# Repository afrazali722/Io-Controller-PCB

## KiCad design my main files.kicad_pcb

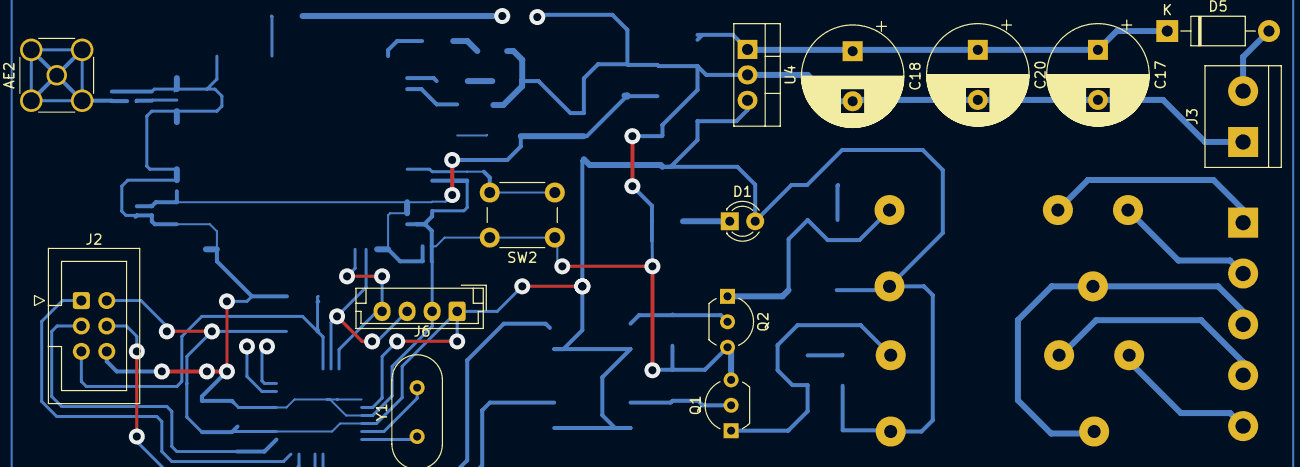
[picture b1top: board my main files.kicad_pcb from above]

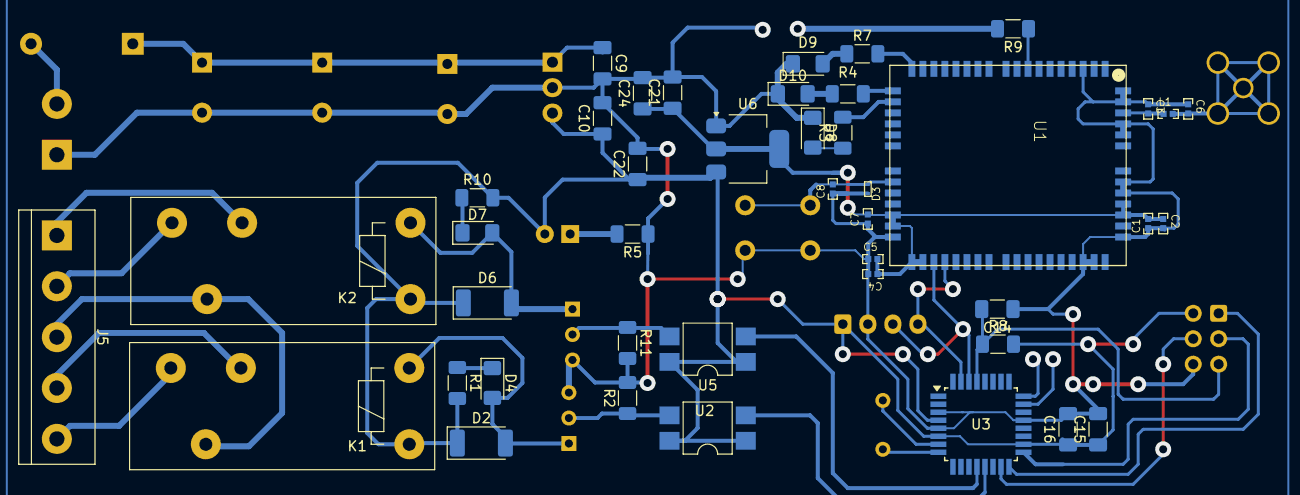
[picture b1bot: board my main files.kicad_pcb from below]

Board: 2 copper layers, 57 parts (43 on the bottom side), 37 nets.

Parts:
AE2: Antenna_Shield; SMA_Wurth_60312002114503_Vertical
C1, C4: 2.2uF; C0402
C2, C5, C7: 0.1uF; C0402
C3, C6: NC; C0402
C8: 330pF; C0402
C9, C14, C16, C22: 1uF; C_1206_3216Metric_Pad1.33x1.80mm_HandSolder
C10, C21: 10uF; C_1206_3216Metric_Pad1.33x1.80mm_HandSolder
C15, C24: 100nF; C_1206_3216Metric_Pad1.33x1.80mm_HandSolder
C17, C18, C20: 4700uF; CP_Radial_D10.0mm_P5.00mm
D1: LED; LED_D3.0mm
D2, D6: SM4007; D_MELF
D3: ESD7951ST5G; SOD−923
D4, D7, D8, D9, D10: LED; LED_1206_3216Metric_Pad1.42x1.75mm_HandSolder
D5: 1N5819; D_DO-41_SOD81_P10.16mm_Horizontal
J2: AVR-ISP-6; IDC-Header_2x03_P2.54mm_Vertical
J3: Screw_Terminal_01x02; TerminalBlock_bornier-2_P5.08mm
J5: Screw_Terminal_01x05; TerminalBlock_bornier-5_P5.08mm
J6: Conn_01x04_Pin; JST_EH_B4B-EH-A_1x04_P2.50mm_Vertical
K1, K2: Relay_SPDT; Relay_SPDT_Schrack-RT1-FormC_RM3.5mm
L1: 9.1nH; L-0402
Q1, Q2: BC547; TO-92_Inline_Wide
R1, R3, R4, R5, R7, R9, R10: 1K; R_1206_3216Metric_Pad1.30x1.75mm_HandSolder
R2, R8, R11: 10k; R_1206_3216Metric_Pad1.30x1.75mm_HandSolder
SW2: SW_Push; SW_PUSH_6mm_H4.3mm
U1: LoRaWAN IC; LA66_APPLICATION_FRAME
U2, U5: PC817; SMDIP-4_W7.62mm
U3: ATmega8-16A; TQFP-32_7x7mm_P0.8mm
U4: L7805; TO-220-3_Vertical
U6: AMS1117-3.3; SOT-223-3_TabPin2
Y1: Crystal; Crystal_HC49-4H_Vertical

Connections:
+3.3V: C1.2, C2.1, C4.1, C5.2, C7.2, C21.1, C24.1, U1.29 (VDDD), U1.30 (PA9), U1.32 (VBAT_BB@1), U1.33 (VBAT_BB@2), U1.52 (VBAT_RF@1), U1.53 (VBAT_RF@2), U6.2 (VO)
+5VA: C10.1, C15.1, C16.1, C22.1, D1.2 (A), D2.1 (K), D6.1 (K), J2.2 (VCC), J6.1, K1.A1, K2.A1, R1.2, R8.2, R10.2, U2.1, U2.4, U3.4 (VCC), U3.6 (VCC), U3.18 (AVCC), U4.3 (OUT), U5.1, U5.4, U6.3 (VI)
+12V: C9.1, C17.1, C18.1, C20.1, D5.1 (K), U4.1 (IN)
/BOOT: R9.1, U1.8 (PA2)
COM: J5.3, K1.11, K2.11
GNDA: C1.1, C2.2, C3.1, C4.2, C5.1, C6.1, C7.1, C8.1, C9.2, C10.2, C14.1, C15.2, C16.2, C17.2, C18.2, C20.2, C21.2, C22.2, C24.2, D3.P$1 (1), D8.1 (K), D9.1 (K), D10.1 (K), J2.6 (GND), J3.1, J6.2, Q1.3 (E), Q2.3 (E), R2.2, R5.1, R11.2, SW2.1, U1.31 (GND@31), U1.47 (GND@47), U1.48 (GND@48), U1.50 (GND@50), U1.54 (GND@54), U1.55 (GND@55), U1.58 (GND@58), U1.59 (GND@59), U1.61 (GND@61), U1.62 (GND@62), U3.3 (GND), U3.5 (GND), U3.21 (AGND), U4.2 (GND), U6.1 (GND)
MISO: J2.1 (MISO), U3.16 (PB4)
MOSI: J2.4 (MOSI), U3.15 (PB3)
NC: J5.1, K2.12
NC1: J5.4, K1.12
NO: J5.2, K2.14
NO1: J5.5, K1.14
unnamed: AE2.1 (A), AE2.2 (Shield), C6.2, L1.2
unnamed: D1.1 (K), R5.2
unnamed: D2.2 (A), D4.2 (A), K1.A2, Q1.1 (C)
unnamed: D4.1 (K), R1.1
unnamed: D5.2 (A), J3.2
unnamed: D6.2 (A), D7.2 (A), K2.A2, Q2.1 (C)
unnamed: D7.1 (K), R10.1
unnamed: D8.2 (A), R3.1
unnamed: D9.2 (A), R7.1
unnamed: D10.2 (A), R4.1
unnamed: Q1.2 (B), R2.1, U2.3
unnamed: Q2.2 (B), R11.1, U5.3
unnamed: C3.2, L1.1, U1.60 (ANT)
unnamed: U3.7 (PB6/XTAL1), Y1.2
unnamed: U3.8 (PB7/XTAL2), Y1.1
PB12: R4.2, U1.19 (PB12)
PB13: R7.2, U1.18 (PB13)
PB14: R3.2, U1.20 (PB14)
R1: U3.12 (PB0), U5.2
R2: U2.2, U3.13 (PB1)
RESET: C14.2, J2.5 (~RST), R8.1, U3.29 (PC6/~RESET)
RSTN_PIN: C8.2, D3.P$2 (2), SW2.2, U1.26 (RSTN_PIN)
RX: J6.3, U1.34 (PB0), U3.30 (PD0)
SCK: J2.3 (SCK), U3.17 (PB5)
TX: J6.4, U1.35 (PB1), U3.31 (PD1)
